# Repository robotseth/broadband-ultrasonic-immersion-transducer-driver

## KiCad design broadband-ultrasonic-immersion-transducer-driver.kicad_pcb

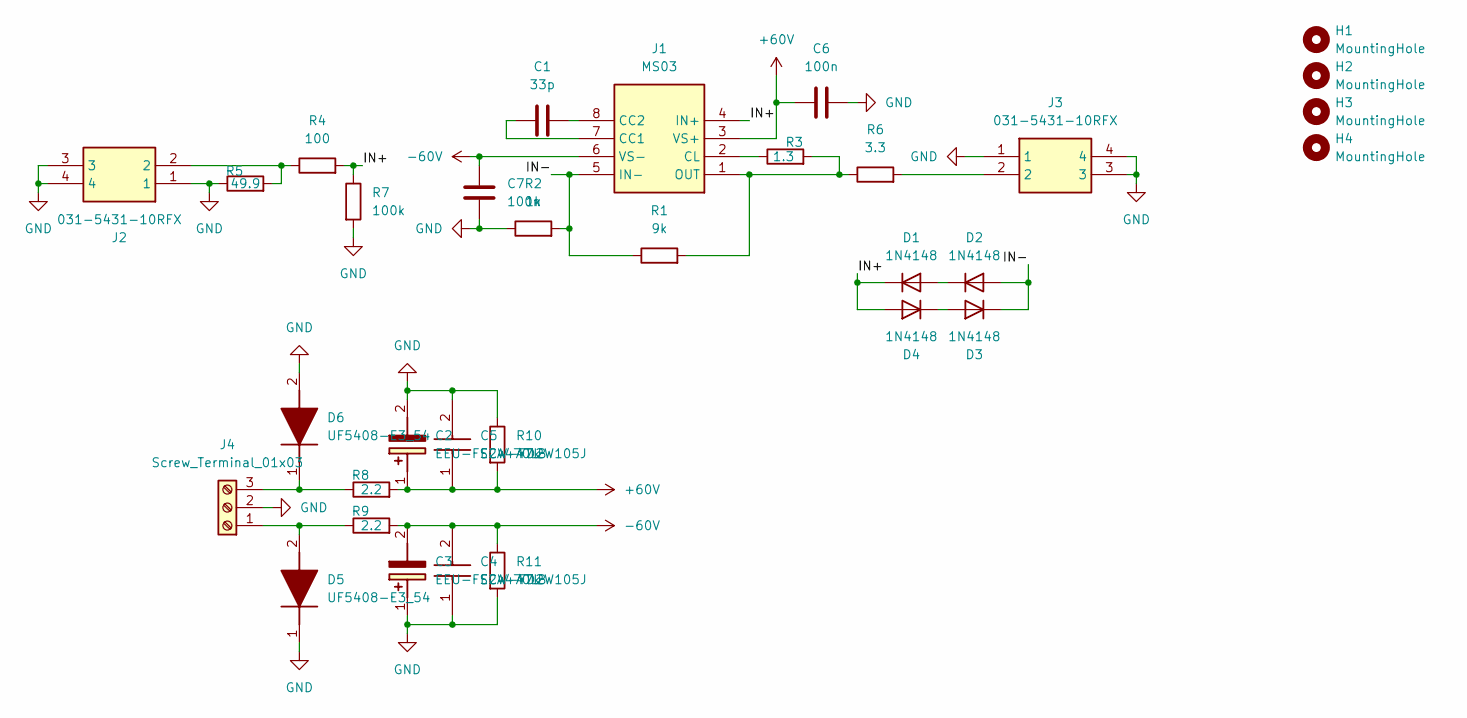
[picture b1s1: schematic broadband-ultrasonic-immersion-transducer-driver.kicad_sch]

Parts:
C1: 33p; C_0805_2012Metric
C2, C3: EEU-FS2A470LB; CAPPRD350W65D800H1650; Mouser Part Number 667-EEU-FS2A470LB
C4, C5: ECW-FD2W105J; ECWFD2W105J; Mouser Part Number 667-ECW-FD2W105J
C6, C7: 100n; C_1206_3216Metric
D1, D2, D3, D4: 1N4148; D_DO-35_SOD27_P7.62mm_Horizontal
D5, D6: UF5408-E3_54; DIOAD2855W132L835D505; Mouser Part Number 625-UF5408-E3
H1, H2, H3, H4: MountingHole; MountingHole_3.2mm_M3_DIN965
J1: MS03; Mouser Part Number N/A
J2, J3: 031-5431-10RFX; 031543110RFX; Mouser Part Number 523-31-5431-10RFX
J4: Screw_Terminal_01x03; TerminalBlock_Phoenix_MKDS-1,5-3_1x03_P5.00mm_Horizontal
R1: 9k; R_0805_2012Metric
R2: 1k; R_0805_2012Metric
R3: 1.3; R_Axial_DIN0309_L9.0mm_D3.2mm_P12.70mm_Horizontal
R4: 100; R_1206_3216Metric
R5: 49.9; R_1206_3216Metric
R6: 3.3; R_2512_6332Metric
R7: 100k; R_1206_3216Metric
R8, R9: 2.2; R_2512_6332Metric
R10, R11: 47k; R_1206_3216Metric

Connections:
+60V: C2.1 (+), C5.1, C6.1, J1.3 (VS+), R8.2, R10.2
-60V: C3.2 (-), C4.2, C7.1, J1.6 (VS-), R9.2, R11.1
/IN+: D1.1 (K), D4.2 (A), J1.4 (IN+), R4.2, R7.1
/IN-: D2.2 (A), D3.1 (K), J1.5 (IN-), R1.1, R2.2
GND: C2.2 (-), C3.1 (+), C4.1, C5.2, C6.2, C7.2, D5.1 (K), D6.2 (A), J2.1, J2.3, J2.4, J3.1, J3.3, J3.4, J4.2, R2.1, R5.1, R7.2, R10.1, R11.2
unnamed: C1.1, J1.7 (CC1)
unnamed: C1.2, J1.8 (CC2)
unnamed: D1.2 (A), D2.1 (K)
unnamed: D3.2 (A), D4.1 (K)
unnamed: D5.2 (A), J4.1, R9.1
unnamed: D6.1 (K), J4.3, R8.1
unnamed: J1.1 (OUT), R1.2, R3.2, R6.1
unnamed: J1.2 (CL), R3.1
unnamed: J2.2, R4.1, R5.2
unnamed: J3.2, R6.2

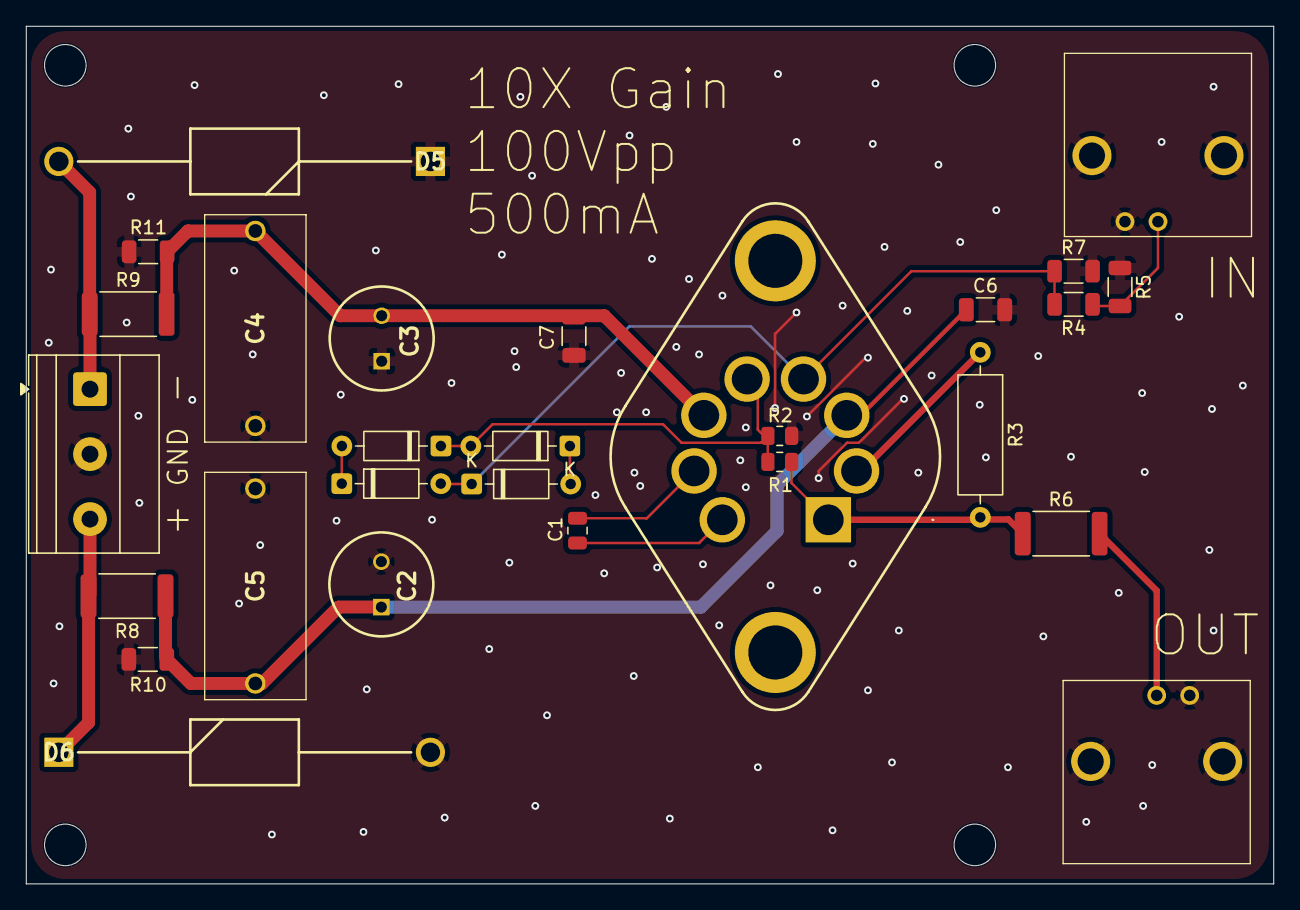
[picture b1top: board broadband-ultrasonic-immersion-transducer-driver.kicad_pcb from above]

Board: 2 copper layers, 96.0 x 66.0 mm, 32 parts (0 on the bottom side), 15 nets.
